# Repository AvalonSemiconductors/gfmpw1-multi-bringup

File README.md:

# GFMPW-1 Multi-project die bring-up

Contains all the files and tools used by me to bring up my [multi-project submission](https://github.com/AvalonSemiconductors/gfmpw1-multi) to GFMPW-1.

[Docs can be found here](https://avalonsemiconductors.github.io/GFMPW-1-MULTI/index.html)

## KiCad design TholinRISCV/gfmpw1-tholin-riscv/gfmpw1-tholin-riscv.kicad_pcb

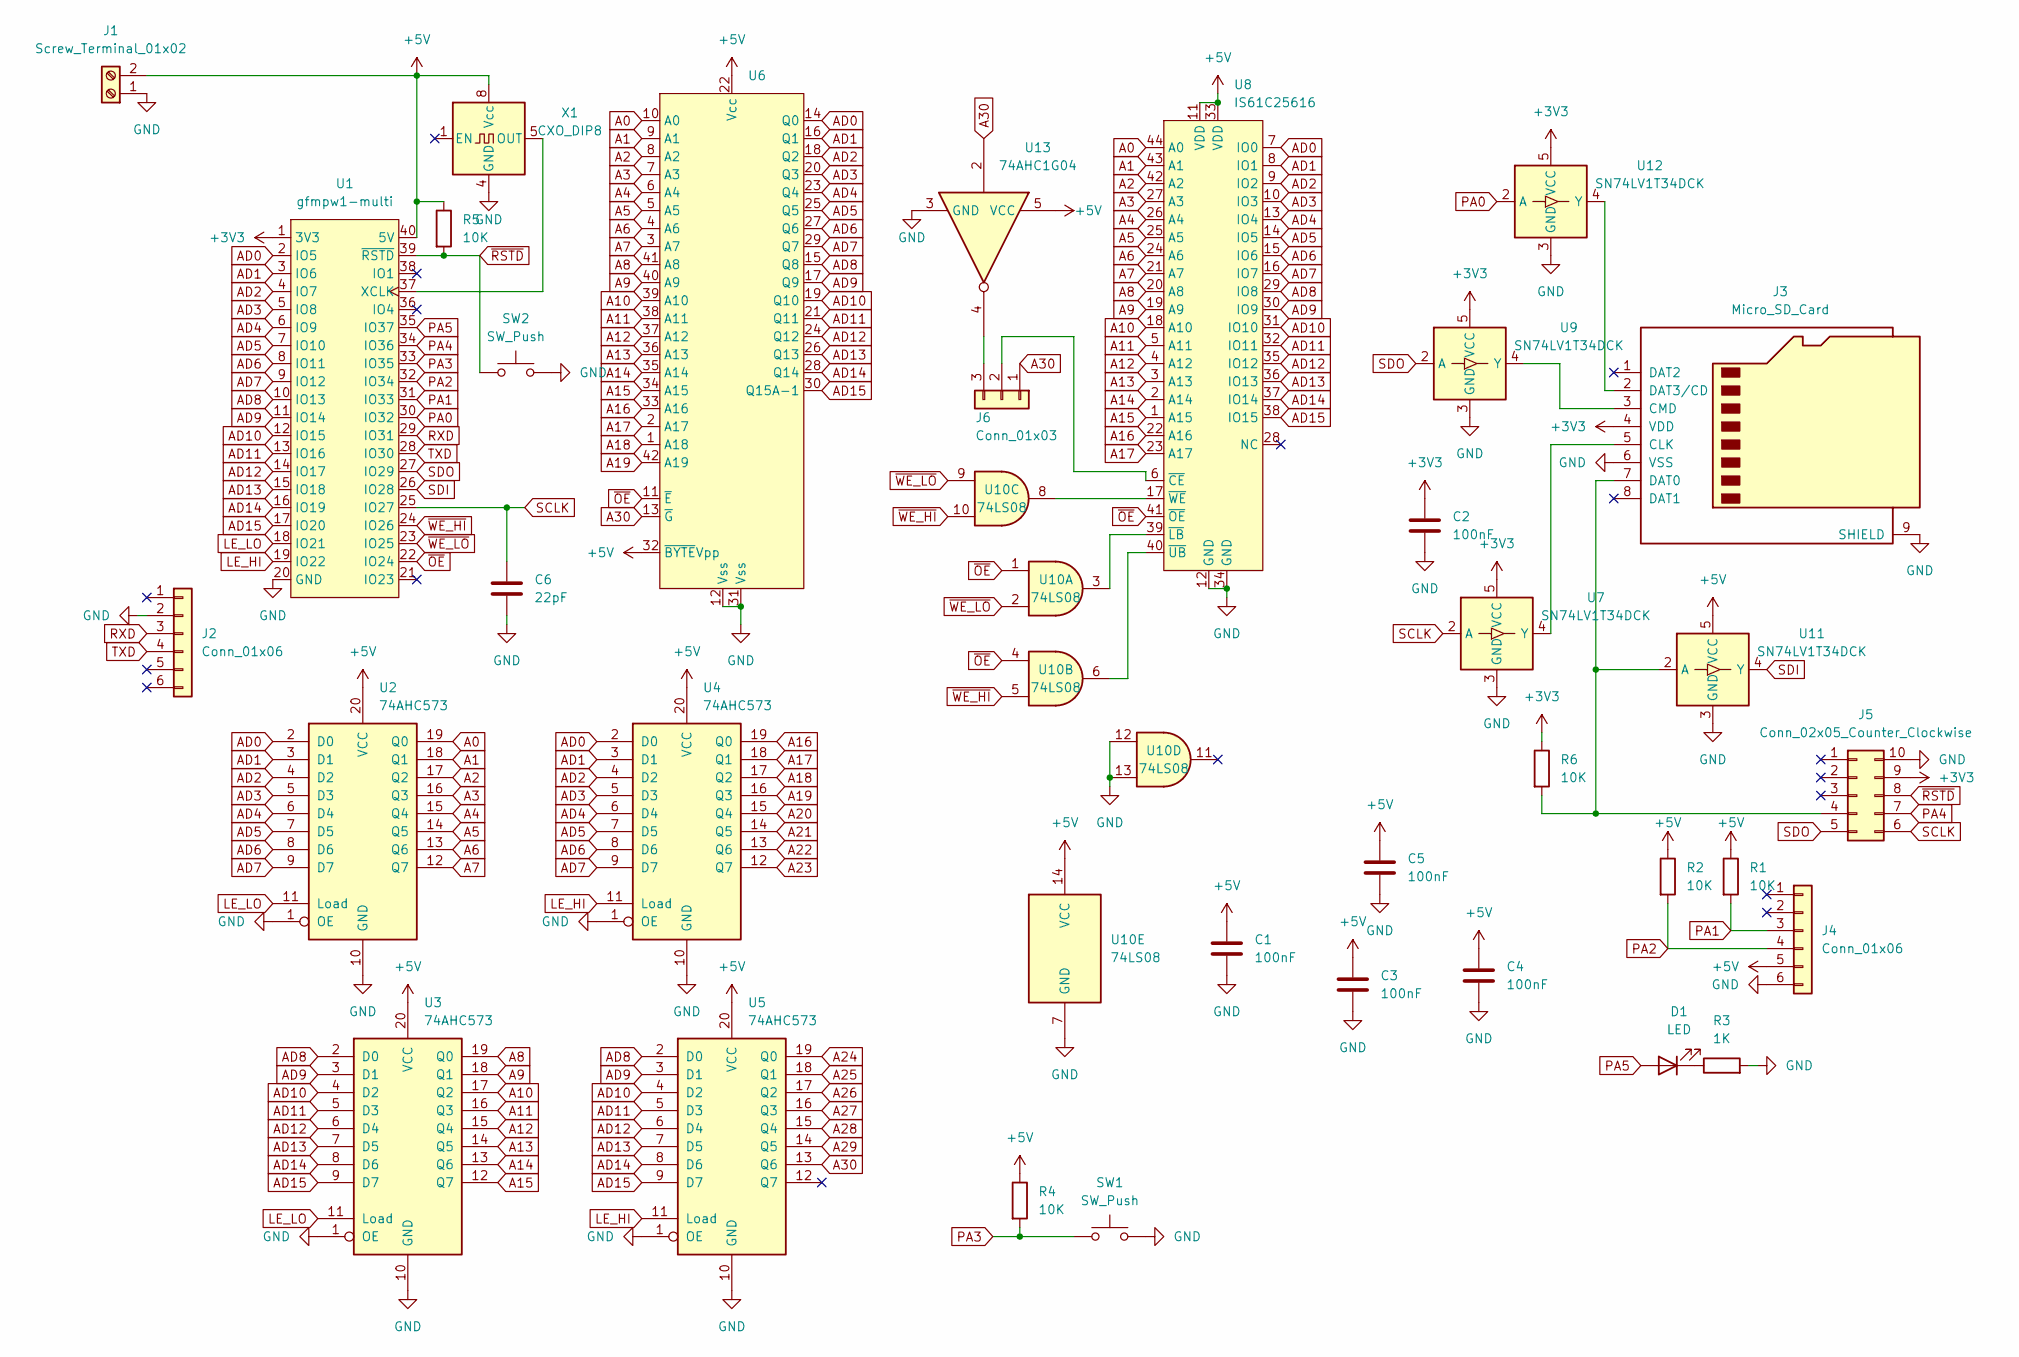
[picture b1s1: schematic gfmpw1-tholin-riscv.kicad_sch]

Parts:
C1, C2, C3, C4, C5: 100nF; C_Disc_D3.8mm_W2.6mm_P2.50mm
C6: 22pF; C_Disc_D3.8mm_W2.6mm_P2.50mm
D1: LED; LED_D5.0mm
J1: Screw_Terminal_01x02; TerminalBlock_bornier-2_P5.08mm
J2: Conn_01x06; PinSocket_1x06_P2.54mm_Vertical
J3: Micro_SD_Card; microSD_HC_Hirose_DM3AT-SF-PEJM5
J4: Conn_01x06; PinHeader_1x06_P2.54mm_Vertical
J5: Conn_02x05_Counter_Clockwise; PinHeader_2x05_P2.54mm_Vertical
J6: Conn_01x03; PinHeader_1x03_P2.54mm_Vertical
R1, R2, R4, R5, R6: 10K; R_Axial_DIN0204_L3.6mm_D1.6mm_P7.62mm_Horizontal
R3: 1K; R_Axial_DIN0204_L3.6mm_D1.6mm_P7.62mm_Horizontal
SW1, SW2: SW_Push; SW_PUSH_6mm
U1: gfmpw1-multi; DIP-40_W15.24mm_Socket
U2, U3, U4, U5: 74AHC573; TSSOP-20_4.4x6.5mm_P0.65mm
U6: DIP-42_W15.24mm
U7, U9, U11, U12: SN74LV1T34DCK; SOT-23-5
U8: IS61C25616; TSOP-II-44_10.16x18.41mm_P0.8mm
U10: 74LS08; SO-14_3.9x8.65mm_P1.27mm
U13: 74AHC1G04; SOIC-6
X1: CXO_DIP8; Oscillator_DIP-8

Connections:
+3V3: C2.1, J3.4 (VDD), J5.9, R6.1, U1.1 (3V3), U7.5 (VCC), U9.5 (VCC), U12.5 (VCC)
+5V: C1.1, C3.1, C4.1, C5.1, J1.2, J4.5, R1.1, R2.1, R4.1, R5.1, U1.40 (5V), U2.20 (VCC), U3.20 (VCC), U4.20 (VCC), U5.20 (VCC), U6.22 (Vcc), U6.32 (~BYTEVpp), U8.11 (VDD), U8.33 (VDD), U10.14 (VCC), U11.5 (VCC), U13.5 (VCC), X1.8 (Vcc)
A0: U2.19 (Q0), U6.10 (A0), U8.44 (A0)
A1: U2.18 (Q1), U6.9 (A1), U8.43 (A1)
A2: U2.17 (Q2), U6.8 (A2), U8.42 (A2)
A3: U2.16 (Q3), U6.7 (A3), U8.27 (A3)
A4: U2.15 (Q4), U6.6 (A4), U8.26 (A4)
A5: U2.14 (Q5), U6.5 (A5), U8.25 (A5)
A6: U2.13 (Q6), U6.4 (A6), U8.24 (A6)
A7: U2.12 (Q7), U6.3 (A7), U8.21 (A7)
A8: U3.19 (Q0), U6.41 (A8), U8.20 (A8)
A9: U3.18 (Q1), U6.40 (A9), U8.19 (A9)
A10: U3.17 (Q2), U6.39 (A10), U8.18 (A10)
A11: U3.16 (Q3), U6.38 (A11), U8.5 (A11)
A12: U3.15 (Q4), U6.37 (A12), U8.4 (A12)
A13: U3.14 (Q5), U6.36 (A13), U8.3 (A13)
A14: U3.13 (Q6), U6.35 (A14), U8.2 (A14)
A15: U3.12 (Q7), U6.34 (A15), U8.1 (A15)
A16: U4.19 (Q0), U6.33 (A16), U8.22 (A16)
A17: U4.18 (Q1), U6.2 (A17), U8.23 (A17)
A18: U4.17 (Q2), U6.1 (A18)
A19: U4.16 (Q3), U6.42 (A19)
A20: U4.15 (Q4)
A21: U4.14 (Q5)
A22: U4.13 (Q6)
A23: U4.12 (Q7)
A24: U5.19 (Q0)
A25: U5.18 (Q1)
A26: U5.17 (Q2)
A27: U5.16 (Q3)
A28: U5.15 (Q4)
A29: U5.14 (Q5)
A30: J6.1, U5.13 (Q6), U6.13 (~G), U13.2
AD0: U1.2 (IO5), U2.2 (D0), U4.2 (D0), U6.14 (Q0), U8.7 (IO0)
AD1: U1.3 (IO6), U2.3 (D1), U4.3 (D1), U6.16 (Q1), U8.8 (IO1)
AD2: U1.4 (IO7), U2.4 (D2), U4.4 (D2), U6.18 (Q2), U8.9 (IO2)
AD3: U1.5 (IO8), U2.5 (D3), U4.5 (D3), U6.20 (Q3), U8.10 (IO3)
AD4: U1.6 (IO9), U2.6 (D4), U4.6 (D4), U6.23 (Q4), U8.13 (IO4)
AD5: U1.7 (IO10), U2.7 (D5), U4.7 (D5), U6.25 (Q5), U8.14 (IO5)
AD6: U1.8 (IO11), U2.8 (D6), U4.8 (D6), U6.27 (Q6), U8.15 (IO6)
AD7: U1.9 (IO12), U2.9 (D7), U4.9 (D7), U6.29 (Q7), U8.16 (IO7)
AD8: U1.10 (IO13), U3.2 (D0), U5.2 (D0), U6.15 (Q8), U8.29 (IO8)
AD9: U1.11 (IO14), U3.3 (D1), U5.3 (D1), U6.17 (Q9), U8.30 (IO9)
AD10: U1.12 (IO15), U3.4 (D2), U5.4 (D2), U6.19 (Q10), U8.31 (IO10)
AD11: U1.13 (IO16), U3.5 (D3), U5.5 (D3), U6.21 (Q11), U8.32 (IO11)
AD12: U1.14 (IO17), U3.6 (D4), U5.6 (D4), U6.24 (Q12), U8.35 (IO12)
AD13: U1.15 (IO18), U3.7 (D5), U5.7 (D5), U6.26 (Q13), U8.36 (IO13)
AD14: U1.16 (IO19), U3.8 (D6), U5.8 (D6), U6.28 (Q14), U8.37 (IO14)
AD15: U1.17 (IO20), U3.9 (D7), U5.9 (D7), U6.30 (Q15A-1), U8.38 (IO15)
GND: C1.2, C2.2, C3.2, C4.2, C5.2, C6.2, J1.1, J2.2, J3.6 (VSS), J3.9 (SHIELD), J4.6, J5.10, R3.2, SW1.2, SW2.2, U1.20 (GND), U2.1 (OE), U2.10 (GND), U3.1 (OE), U3.10 (GND), U4.1 (OE), U4.10 (GND), U5.1 (OE), U5.10 (GND), U6.12 (Vss), U6.31 (Vss), U7.3 (GND), U8.12 (GND), U8.34 (GND), U9.3 (GND), U10.7 (GND), U10.12, U10.13, U11.3 (GND), U12.3 (GND), U13.3 (GND), X1.4 (GND)
LE_HI: U1.19 (IO22), U4.11 (Load), U5.11 (Load)
LE_LO: U1.18 (IO21), U2.11 (Load), U3.11 (Load)
unnamed: D1.1 (K), R3.1
unnamed: J3.5 (CLK), U7.4 (Y)
unnamed: J3.3 (CMD), U9.4 (Y)
unnamed: J3.7 (DAT0), J5.4, R6.2, U11.2 (A)
unnamed: J3.2 (DAT3/CD), U12.4 (Y)
unnamed: J6.2, U8.6 (~CE)
unnamed: J6.3, U13.4
unnamed: U1.37 (XCLK), X1.5 (OUT)
unnamed: U8.39 (~LB), U10.3
unnamed: U8.40 (~UB), U10.6
unnamed: U8.17 (~WE), U10.8
PA0: U1.30 (IO32), U12.2 (A)
PA1: J4.3, R1.2, U1.31 (IO33)
PA2: J4.4, R2.2, U1.32 (IO34)
PA3: R4.2, SW1.1, U1.33 (IO35)
PA4: J5.7, U1.34 (IO36)
PA5: D1.2 (A), U1.35 (IO37)
RXD: J2.3, U1.29 (IO31)
SCLK: C6.1, J5.6, U1.25 (IO27), U7.2 (A)
SDI: U1.26 (IO28), U11.4 (Y)
SDO: J5.5, U1.27 (IO29), U9.2 (A)
TXD: J2.4, U1.28 (IO30)
~OE: U1.22 (IO24), U6.11 (~E), U8.41 (~OE), U10.1, U10.4
~RSTD: J5.8, R5.2, SW2.1, U1.39 (~RSTD)
~WE_HI: U1.24 (IO26), U10.5, U10.10
~WE_LO: U1.23 (IO25), U10.2, U10.9

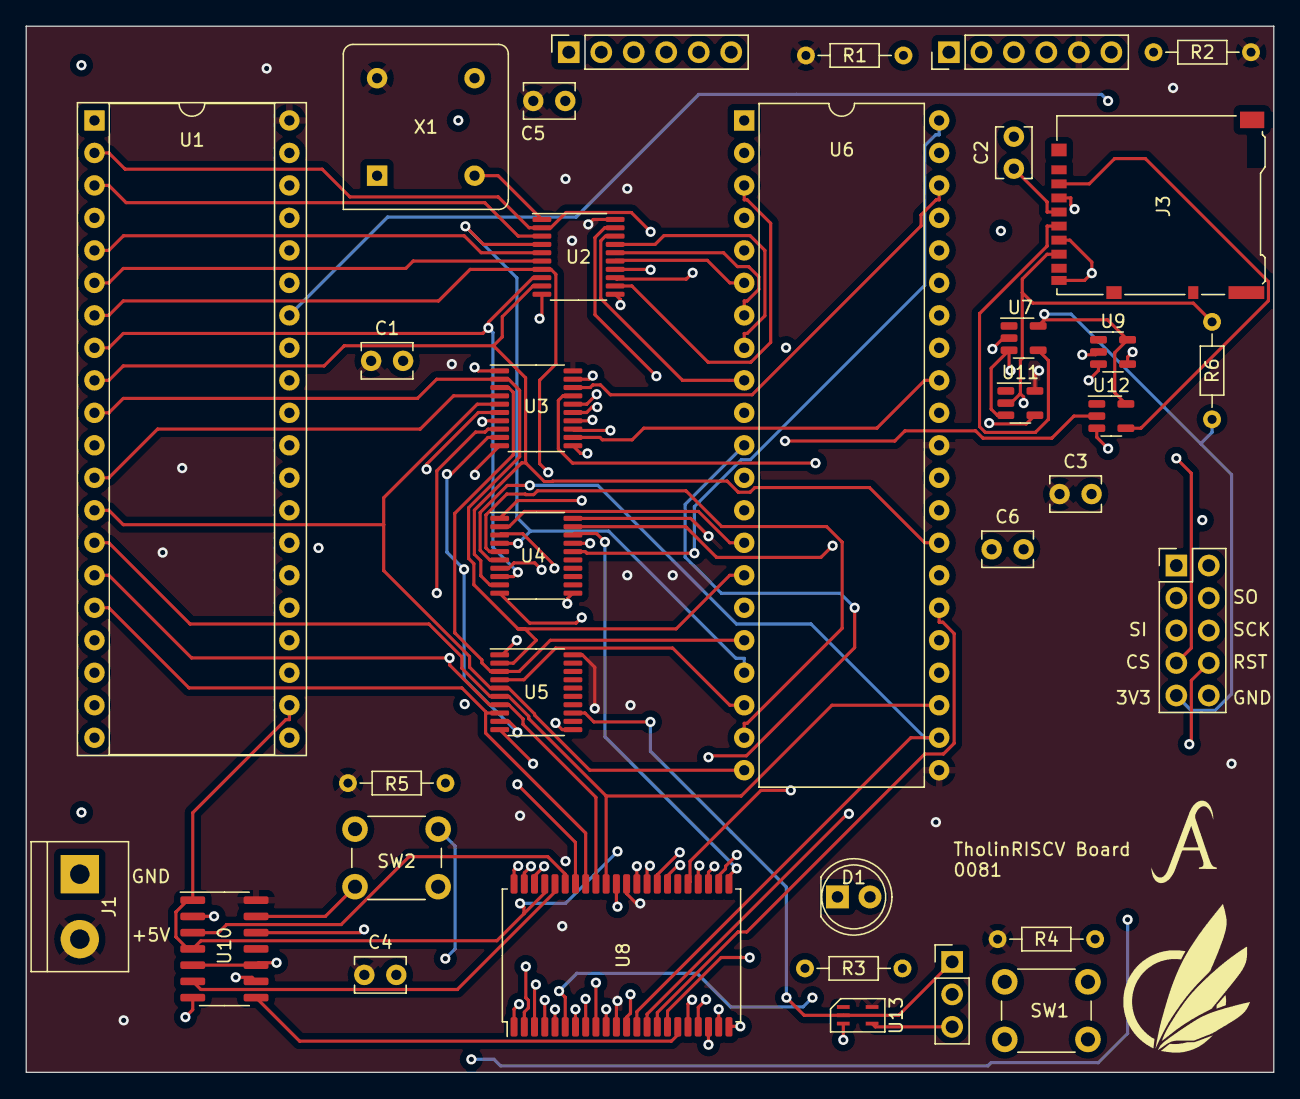
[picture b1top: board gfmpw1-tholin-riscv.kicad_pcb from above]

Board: 4 copper layers, 97.5 x 81.8 mm, 35 parts (0 on the bottom side), 68 nets.

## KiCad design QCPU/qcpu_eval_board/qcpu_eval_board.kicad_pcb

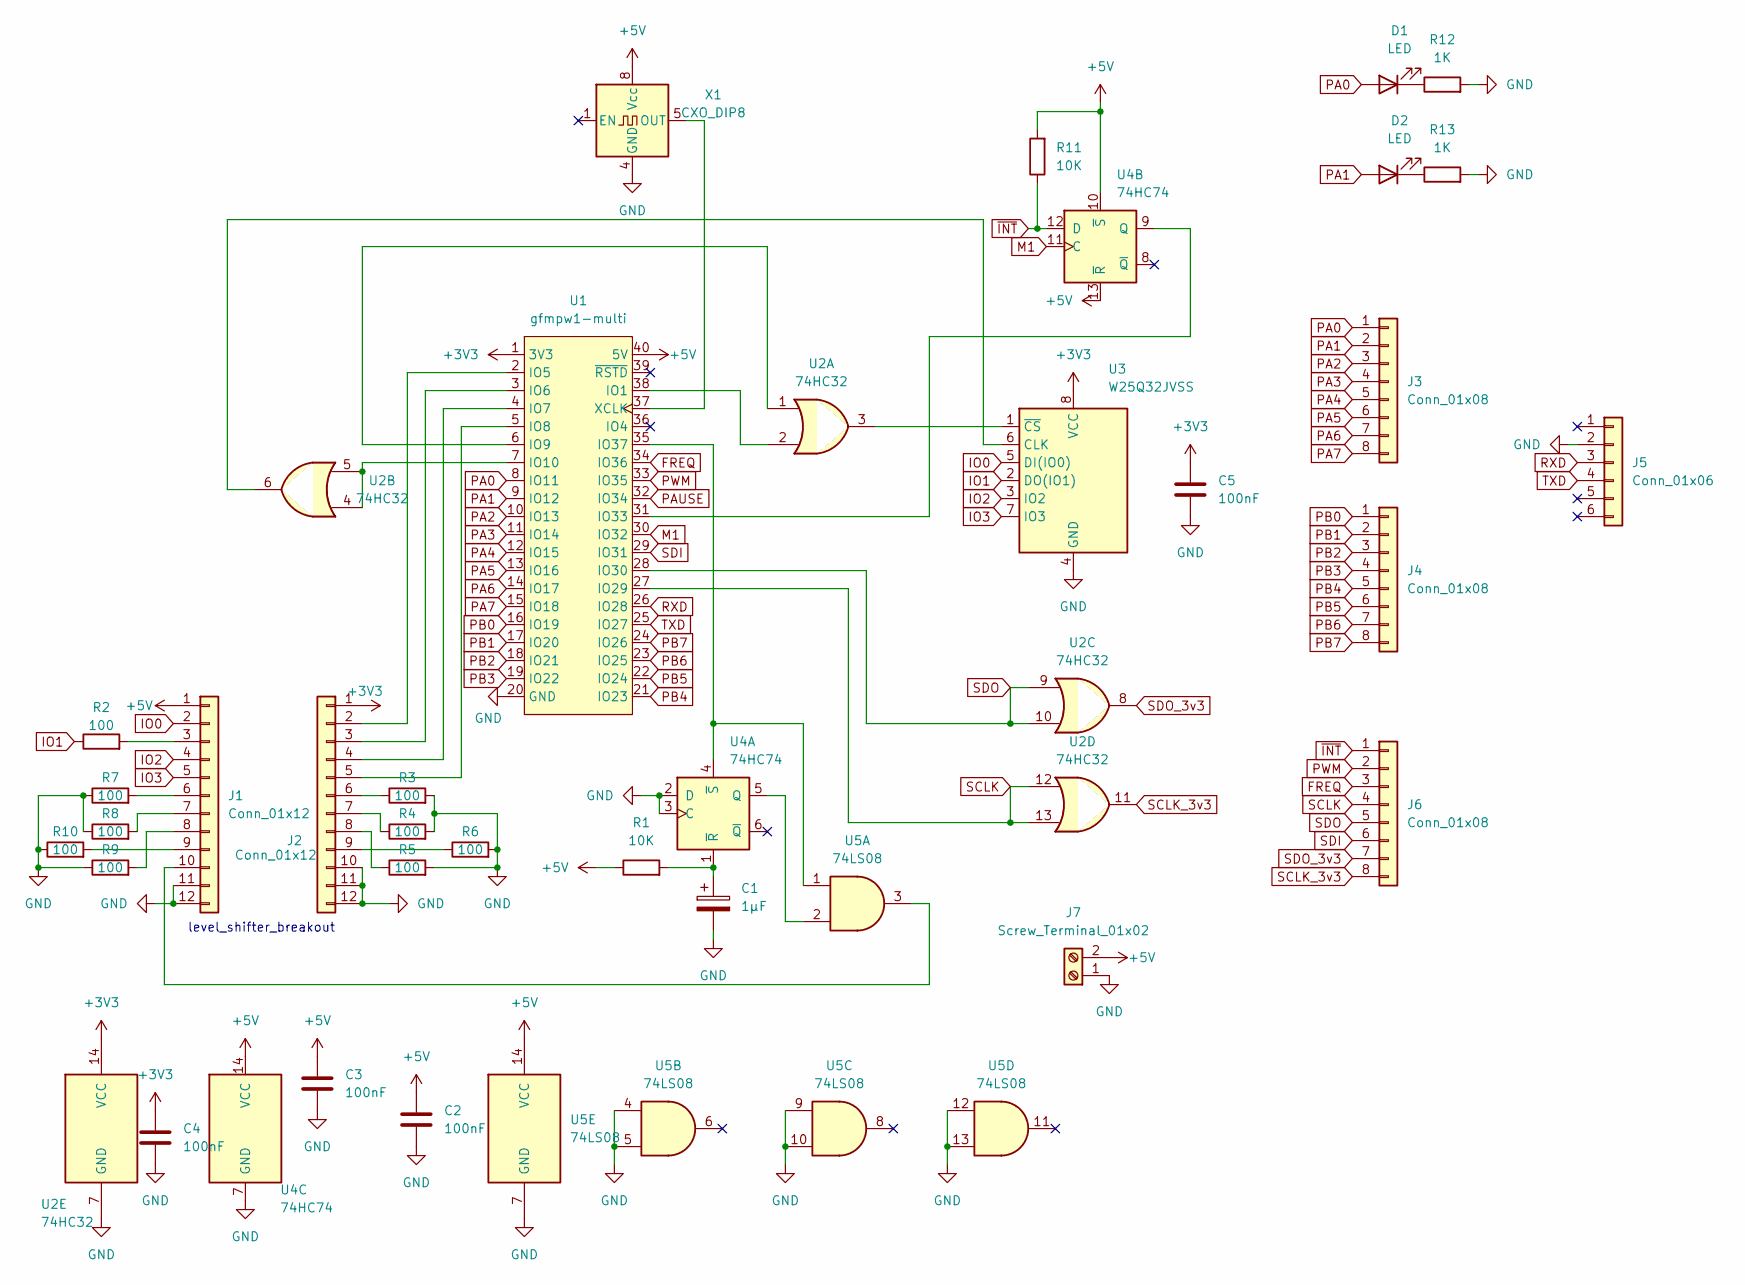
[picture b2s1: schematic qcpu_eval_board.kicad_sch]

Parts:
C1: 1µF; CP_Radial_D4.0mm_P2.00mm
C2, C3, C4, C5: 100nF; C_Disc_D3.8mm_W2.6mm_P2.50mm
D1, D2: LED; LED_D5.0mm
J1, J2: Conn_01x12; PinHeader_1x12_P2.54mm_Vertical
J3, J4, J6: Conn_01x08; PinHeader_1x08_P2.54mm_Vertical
J5: Conn_01x06; PinSocket_1x06_P2.54mm_Vertical
J7: Screw_Terminal_01x02; TerminalBlock_bornier-2_P5.08mm
R1, R11: 10K; R_Axial_DIN0204_L3.6mm_D1.6mm_P7.62mm_Horizontal
R2, R3, R4, R5, R6, R7, R8, R9, R10: 100; R_Axial_DIN0204_L3.6mm_D1.6mm_P7.62mm_Horizontal
R12, R13: 1K; R_Axial_DIN0204_L3.6mm_D1.6mm_P7.62mm_Horizontal
U1: gfmpw1-multi; DIP-40_W15.24mm_Socket
U2: 74HC32; DIP-14_W7.62mm
U3: W25Q32JVSS; DIP-8_W7.62mm
U4: 74HC74; DIP-14_W7.62mm
U5: 74LS08; DIP-14_W7.62mm
X1: CXO_DIP8; Oscillator_DIP-8

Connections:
+3V3: C4.1, C5.1, J2.1, U1.1 (3V3), U2.14 (VCC), U3.8 (VCC)
+5V: C2.1, C3.1, J1.1, J7.2, R1.1, R11.2, U1.40 (5V), U4.10 (~S), U4.13 (~R), U4.14 (VCC), U5.14 (VCC), X1.8 (Vcc)
FREQ: J6.3, U1.34 (IO36)
GND: C1.2, C2.2, C3.2, C4.2, C5.2, J1.11, J1.12, J2.10, J2.11, J2.12, J5.2, J7.1, R3.2, R4.2, R5.2, R6.2, R7.1, R8.1, R9.1, R10.1, R12.2, R13.2, U1.20 (GND), U2.7 (GND), U3.4 (GND), U4.2 (D), U4.3 (C), U4.7 (GND), U5.4, U5.5, U5.7 (GND), U5.9, U5.10, U5.12, U5.13, X1.4 (GND)
IO0: J1.2, U3.5 (DI(IO0))
IO1: R2.1, U3.2 (DO(IO1))
IO2: J1.4, U3.3 (IO2)
IO3: J1.5, U3.7 (IO3)
M1: U1.30 (IO32), U4.11 (C)
unnamed: D1.1 (K), R12.1
unnamed: D2.1 (K), R13.1
unnamed: J1.3, R2.2
unnamed: J1.6, R7.2
unnamed: J1.7, R8.2
unnamed: J1.8, R9.2
unnamed: J1.9, R10.2
unnamed: J1.10, U5.3
unnamed: J2.2, U1.2 (IO5)
unnamed: J2.3, U1.3 (IO6)
unnamed: J2.4, U1.4 (IO7)
unnamed: J2.5, U1.5 (IO8)
unnamed: J2.6, R3.1
unnamed: J2.7, R4.1
unnamed: J2.8, R5.1
unnamed: J2.9, R6.1
unnamed: U1.38 (IO1), U2.2
unnamed: U1.6 (IO9), U2.1
unnamed: U1.7 (IO10), U2.4, U2.5
unnamed: U1.31 (IO33), U4.9 (Q)
unnamed: U1.35 (IO37), U4.4 (~S), U5.1
unnamed: U1.37 (XCLK), X1.5 (OUT)
unnamed: U2.6, U3.6 (CLK)
unnamed: U2.3, U3.1 (~CS)
unnamed: U4.5 (Q), U5.2
unnamed: C1.1, R1.2, U4.1 (~R)
PA0: D1.2 (A), J3.1, U1.8 (IO11)
PA1: D2.2 (A), J3.2, U1.9 (IO12)
PA2: J3.3, U1.10 (IO13)
PA3: J3.4, U1.11 (IO14)
PA4: J3.5, U1.12 (IO15)
PA5: J3.6, U1.13 (IO16)
PA6: J3.7, U1.14 (IO17)
PA7: J3.8, U1.15 (IO18)
PAUSE: U1.32 (IO34)
PB0: J4.1, U1.16 (IO19)
PB1: J4.2, U1.17 (IO20)
PB2: J4.3, U1.18 (IO21)
PB3: J4.4, U1.19 (IO22)
PB4: J4.5, U1.21 (IO23)
PB5: J4.6, U1.22 (IO24)
PB6: J4.7, U1.23 (IO25)
PB7: J4.8, U1.24 (IO26)
PWM: J6.2, U1.33 (IO35)
RXD: J5.3, U1.26 (IO28)
SCLK: J6.4, U1.27 (IO29), U2.12, U2.13
SCLK_3v3: J6.8, U2.11
SDI: J6.6, U1.29 (IO31)
SDO: J6.5, U1.28 (IO30), U2.9, U2.10
SDO_3v3: J6.7, U2.8
TXD: J5.4, U1.25 (IO27)
~INT: J6.1, R11.1, U4.12 (D)

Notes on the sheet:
level_shifter_breakout

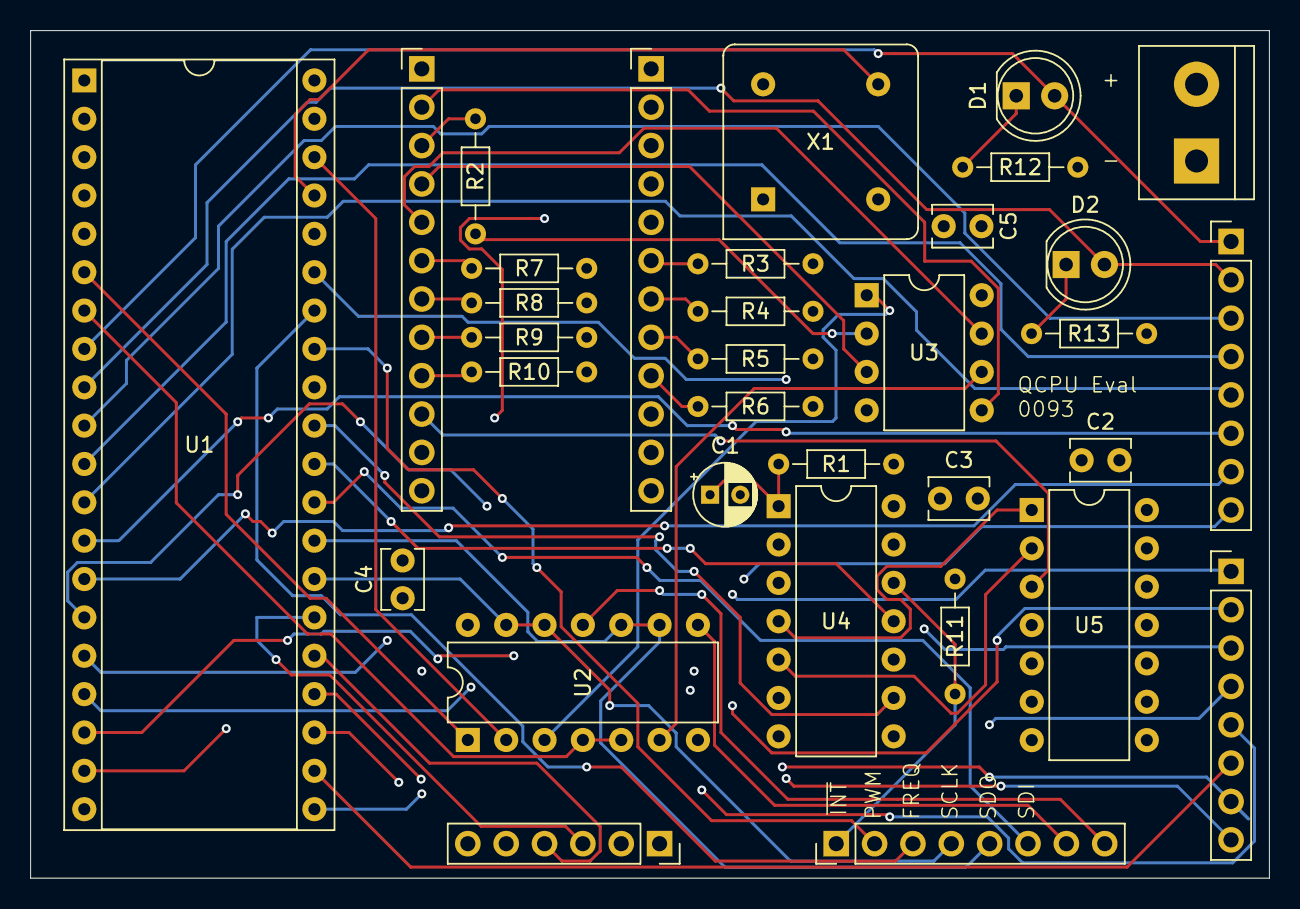
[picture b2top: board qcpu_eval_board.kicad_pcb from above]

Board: 4 copper layers, 82.0 x 56.1 mm, 33 parts (0 on the bottom side), 60 nets.

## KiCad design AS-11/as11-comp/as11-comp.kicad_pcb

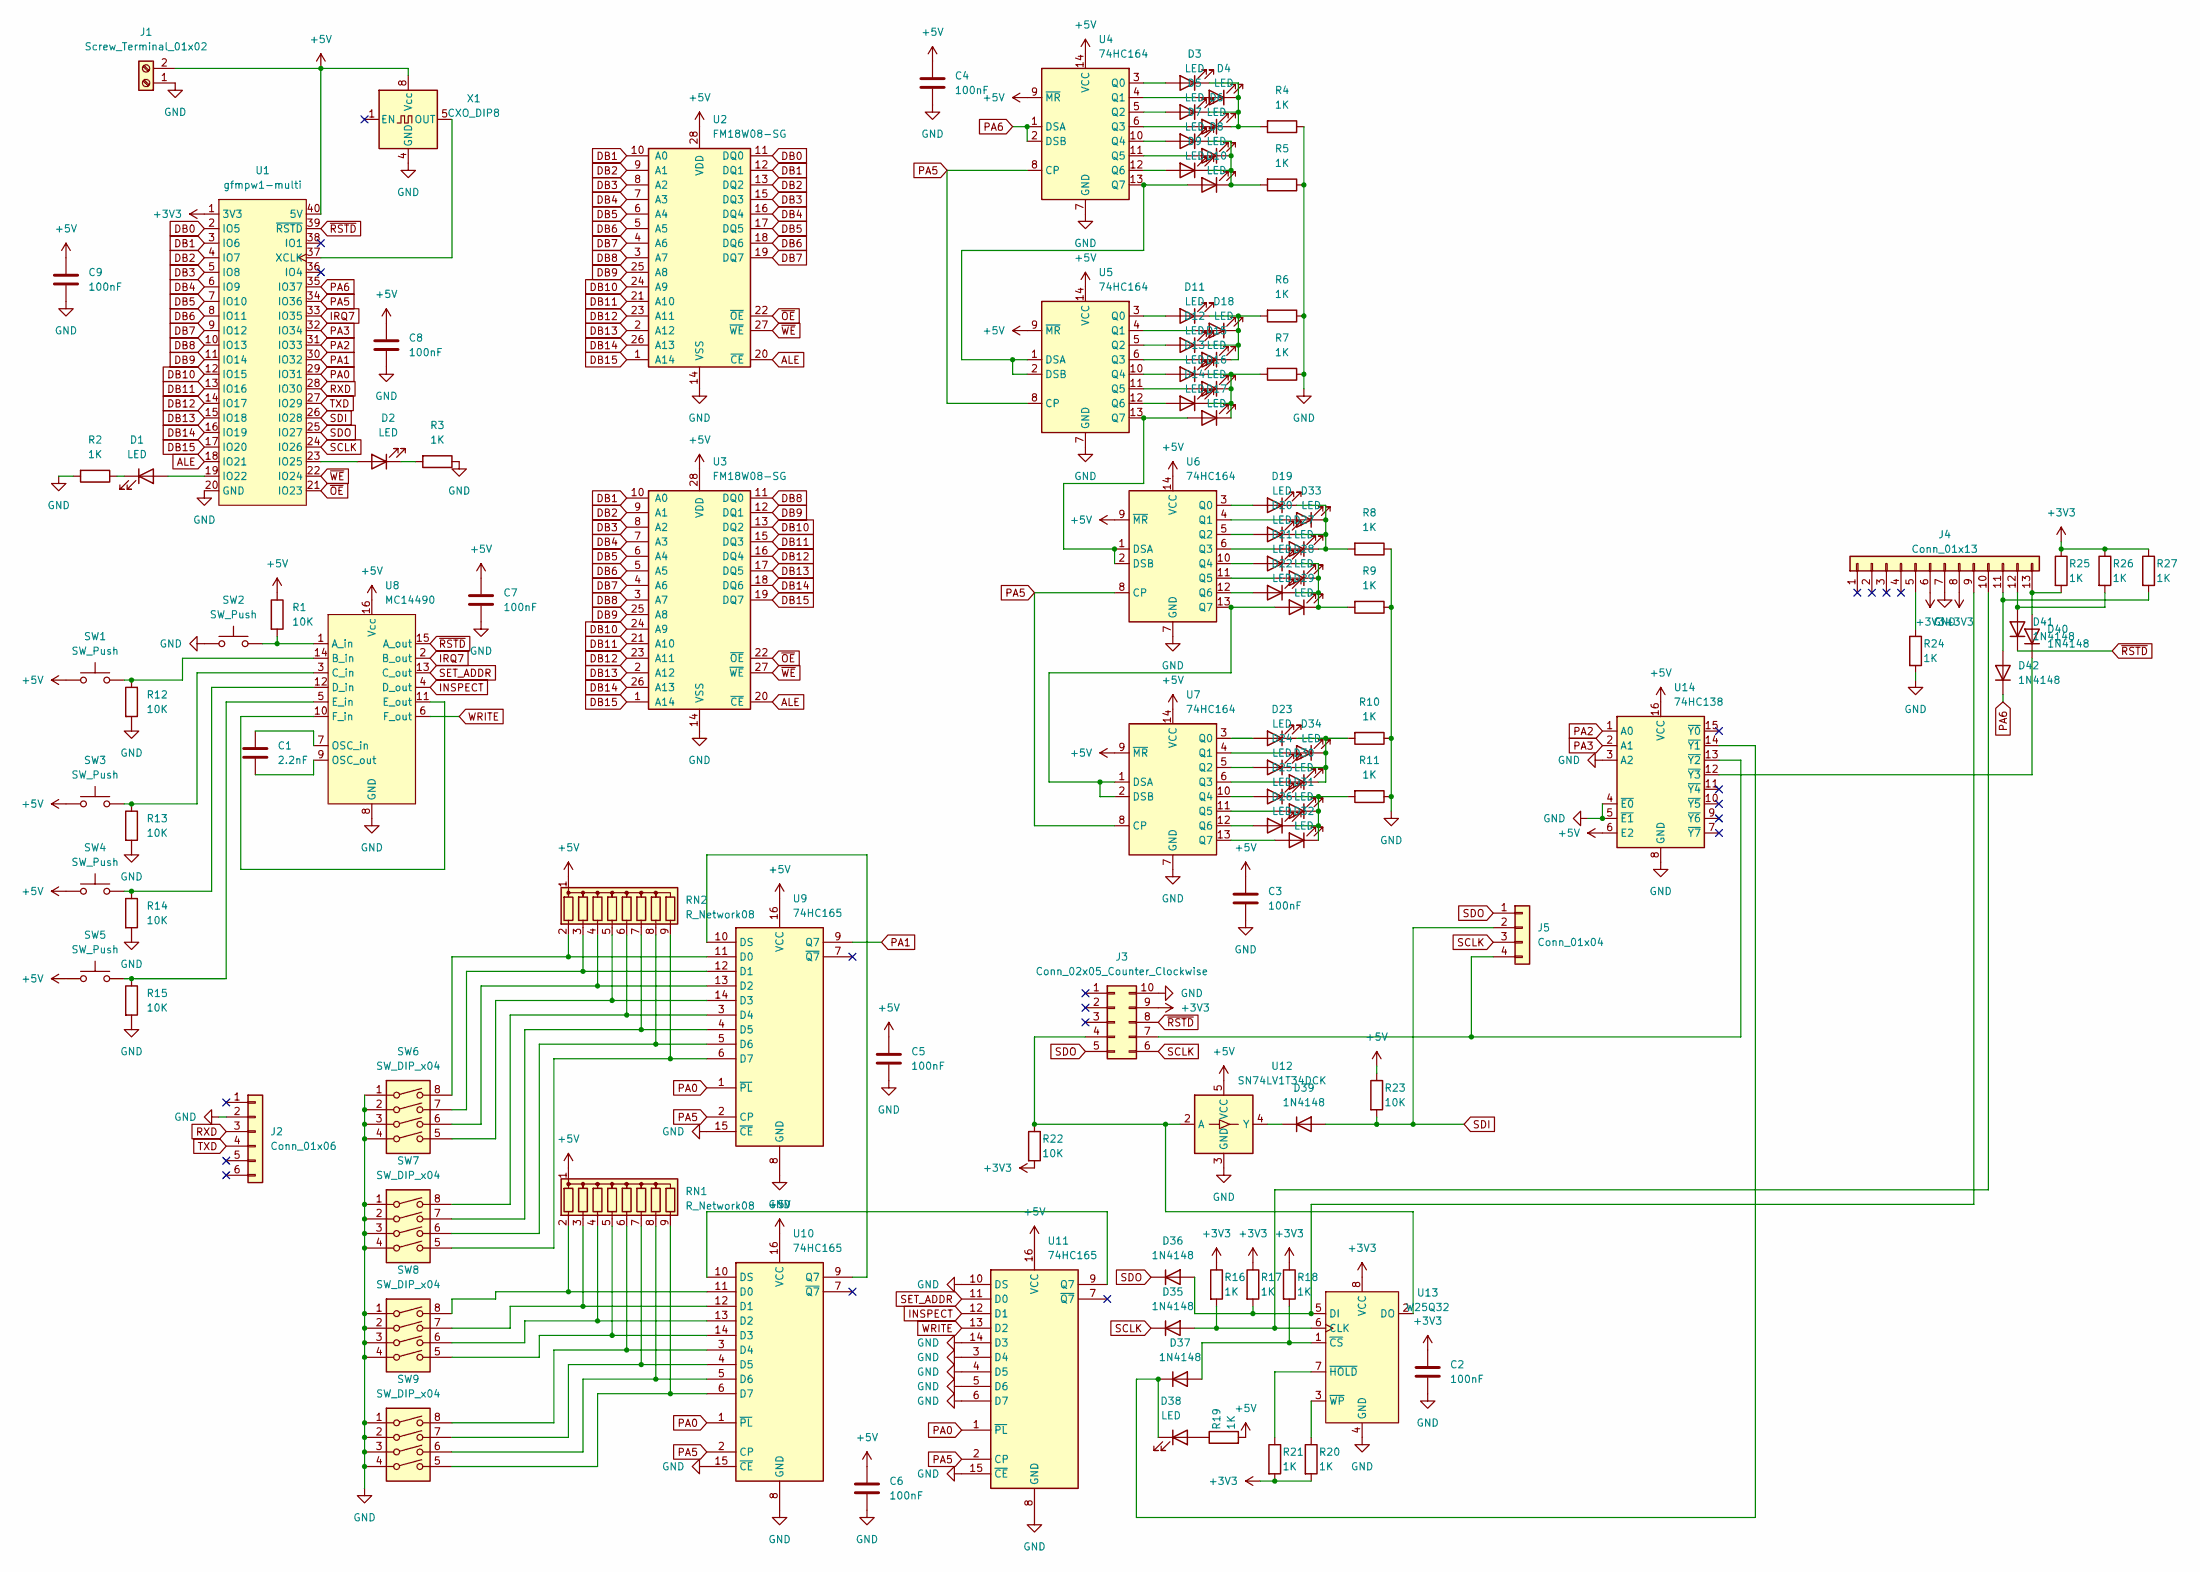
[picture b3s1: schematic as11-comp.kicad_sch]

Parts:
C1: 2.2nF; C_Disc_D3.8mm_W2.6mm_P2.50mm
C2, C3, C4, C5, C6, C7, C8, C9: 100nF; C_Disc_D3.4mm_W2.1mm_P2.50mm
D1, D2, D3, D4, D5, D6, D7, D8, D9, D10, D11, D12, D13, D14, D15, D16, D17, D18, D19, D20, D21, D22, D23, D24, D25, D26, D27, D28, D29, D30, D31, D32, D33, D34, D38: LED; LED_1206_3216Metric_Pad1.42x1.75mm_HandSolder
D35, D36, D37, D39, D40, D41, D42: 1N4148; D_DO-34_SOD68_P7.62mm_Horizontal
J1: Screw_Terminal_01x02; TerminalBlock_bornier-2_P5.08mm
J2: Conn_01x06; PinSocket_1x06_P2.54mm_Vertical
J3: Conn_02x05_Counter_Clockwise; PinHeader_2x05_P2.54mm_Vertical
J4: Conn_01x13; PinHeader_1x13_P2.54mm_Vertical
J5: Conn_01x04; PinHeader_1x04_P2.54mm_Vertical
R1, R12, R13, R14, R15: 10K; R_Axial_DIN0204_L3.6mm_D1.6mm_P7.62mm_Horizontal
R2, R3, R4, R5, R6, R7, R8, R9, R10, R11, R16, R17, R18, R19, R20, R21, R24, R25, R26, R27: 1K; R_1206_3216Metric_Pad1.30x1.75mm_HandSolder
R22, R23: 10K; R_1206_3216Metric_Pad1.30x1.75mm_HandSolder
RN1, RN2: R_Network08; R_Array_SIP9
SW1, SW2, SW3, SW4, SW5: SW_Push; SW_PUSH_6mm
SW6, SW7, SW8, SW9: SW_DIP_x04; SW_DIP_SPSTx04_Slide_6.7x11.72mm_W8.61mm_P2.54mm_LowProfile
U1: gfmpw1-multi; DIP-40_W15.24mm_Socket
U2, U3: FM18W08-SG; DIP-28_W15.24mm
U4, U5, U6, U7: 74HC164; SO-14_3.9x8.65mm_P1.27mm
U8: MC14490; DIP-16_W7.62mm
U9, U10, U11: 74HC165; SO-16_3.9x9.9mm_P1.27mm
U12: SN74LV1T34DCK; SOT-23-5
U13: W25Q32; DIP-8_W7.62mm
U14: 74HC138; SO-16_3.9x9.9mm_P1.27mm
X1: CXO_DIP8; Oscillator_DIP-8

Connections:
+3V3: C2.1, J3.9, J4.6, J4.8, R16.1, R17.1, R18.1, R20.2, R21.2, R22.2, R25.1, R26.1, R27.1, U1.1 (3V3), U13.8 (VCC)
+5V: C3.1, C4.1, C5.1, C6.1, C7.1, C8.1, C9.1, J1.2, R1.1, R19.2, R23.1, RN1.1 (common), RN2.1 (common), SW1.1, SW3.1, SW4.1, SW5.1, U1.40 (5V), U2.28 (VDD), U3.28 (VDD), U4.9 (~MR), U4.14 (VCC), U5.9 (~MR), U5.14 (VCC), U6.9 (~MR), U6.14 (VCC), U7.9 (~MR), U7.14 (VCC), U8.16 (Vcc), U9.16 (VCC), U10.16 (VCC), U11.16 (VCC), U12.5 (VCC), U14.6 (E2), U14.16 (VCC), X1.8 (Vcc)
ALE: U1.18 (IO21), U2.20 (~CE), U3.20 (~CE)
DB0: U1.2 (IO5), U2.11 (DQ0)
DB1: U1.3 (IO6), U2.10 (A0), U2.12 (DQ1), U3.10 (A0)
DB2: U1.4 (IO7), U2.9 (A1), U2.13 (DQ2), U3.9 (A1)
DB3: U1.5 (IO8), U2.8 (A2), U2.15 (DQ3), U3.8 (A2)
DB4: U1.6 (IO9), U2.7 (A3), U2.16 (DQ4), U3.7 (A3)
DB5: U1.7 (IO10), U2.6 (A4), U2.17 (DQ5), U3.6 (A4)
DB6: U1.8 (IO11), U2.5 (A5), U2.18 (DQ6), U3.5 (A5)
DB7: U1.9 (IO12), U2.4 (A6), U2.19 (DQ7), U3.4 (A6)
DB8: U1.10 (IO13), U2.3 (A7), U3.3 (A7), U3.11 (DQ0)
DB9: U1.11 (IO14), U2.25 (A8), U3.12 (DQ1), U3.25 (A8)
DB10: U1.12 (IO15), U2.24 (A9), U3.13 (DQ2), U3.24 (A9)
DB11: U1.13 (IO16), U2.21 (A10), U3.15 (DQ3), U3.21 (A10)
DB12: U1.14 (IO17), U2.23 (A11), U3.16 (DQ4), U3.23 (A11)
DB13: U1.15 (IO18), U2.2 (A12), U3.2 (A12), U3.17 (DQ5)
DB14: U1.16 (IO19), U2.26 (A13), U3.18 (DQ6), U3.26 (A13)
DB15: U1.17 (IO20), U2.1 (A14), U3.1 (A14), U3.19 (DQ7)
GND: C2.2, C3.2, C4.2, C5.2, C6.2, C7.2, C8.2, C9.2, J1.1, J2.2, J3.10, J4.7, R2.2, R3.1, R4.1, R5.1, R6.1, R7.1, R8.1, R9.1, R10.1, R11.1, R12.2, R13.2, R14.2, R15.2, R24.2, SW2.1, SW6.1, SW6.2, SW6.3, SW6.4, SW7.1, SW7.2, SW7.3, SW7.4, SW8.1, SW8.2, SW8.3, SW8.4, SW9.1, SW9.2, SW9.3, SW9.4, U1.20 (GND), U2.14 (VSS), U3.14 (VSS), U4.7 (GND), U5.7 (GND), U6.7 (GND), U7.7 (GND), U8.8 (GND), U9.8 (GND), U9.15 (~CE), U10.8 (GND), U10.15 (~CE), U11.3 (D4), U11.4 (D5), U11.5 (D6), U11.6 (D7), U11.8 (GND), U11.10 (DS), U11.14 (D3), U11.15 (~CE), U12.3 (GND), U13.4 (GND), U14.3 (A2), U14.4 (~E0), U14.5 (~E1), U14.8 (GND), X1.4 (GND)
INSPECT: U8.4 (D_out), U11.12 (D1)
IRQ7: U1.33 (IO35), U8.2 (B_out)
unnamed: D1.2 (A), U1.19 (IO22)
unnamed: D1.1 (K), R2.1
unnamed: D2.2 (A), U1.23 (IO25)
unnamed: D2.1 (K), R3.2
unnamed: D3.2 (A), U4.3 (Q0)
unnamed: D3.1 (K), D4.1 (K), D5.1 (K), D6.1 (K), R4.2
unnamed: D4.2 (A), U4.4 (Q1)
unnamed: D5.2 (A), U4.5 (Q2)
unnamed: D6.2 (A), U4.6 (Q3)
unnamed: D7.2 (A), U4.10 (Q4)
unnamed: D8.2 (A), U4.11 (Q5)
unnamed: D9.2 (A), U4.12 (Q6)
unnamed: D10.2 (A), U4.13 (Q7), U5.1 (DSA), U5.2 (DSB)
unnamed: D7.1 (K), D8.1 (K), D9.1 (K), D10.1 (K), R5.2
unnamed: D11.2 (A), U5.3 (Q0)
unnamed: D11.1 (K), D12.1 (K), D15.1 (K), D18.1 (K), R6.2
unnamed: D12.2 (A), U5.5 (Q2)
unnamed: D13.2 (A), U5.10 (Q4)
unnamed: D13.1 (K), D14.1 (K), D16.1 (K), D17.1 (K), R7.2
unnamed: D14.2 (A), U5.12 (Q6)
unnamed: D15.2 (A), U5.6 (Q3)
unnamed: D16.2 (A), U5.11 (Q5)
unnamed: D17.2 (A), U5.13 (Q7), U6.1 (DSA), U6.2 (DSB)
unnamed: D18.2 (A), U5.4 (Q1)
unnamed: D19.2 (A), U6.3 (Q0)
unnamed: D19.1 (K), D20.1 (K), D27.1 (K), D33.1 (K), R8.2
unnamed: D20.2 (A), U6.5 (Q2)
unnamed: D21.2 (A), U6.10 (Q4)
unnamed: D21.1 (K), D22.1 (K), D28.1 (K), D29.1 (K), R9.2
unnamed: D22.2 (A), U6.12 (Q6)
unnamed: D23.2 (A), U7.3 (Q0)
unnamed: D23.1 (K), D24.1 (K), D30.1 (K), D34.1 (K), R10.2
unnamed: D24.2 (A), U7.5 (Q2)
unnamed: D25.2 (A), U7.10 (Q4)
unnamed: D25.1 (K), D26.1 (K), D31.1 (K), D32.1 (K), R11.2
unnamed: D26.2 (A), U7.12 (Q6)
unnamed: D27.2 (A), U6.6 (Q3)
unnamed: D28.2 (A), U6.11 (Q5)
unnamed: D29.2 (A), U6.13 (Q7), U7.1 (DSA), U7.2 (DSB)
unnamed: D30.2 (A), U7.6 (Q3)
unnamed: D31.2 (A), U7.11 (Q5)
unnamed: D32.2 (A), U7.13 (Q7)
unnamed: D33.2 (A), U6.4 (Q1)
unnamed: D34.2 (A), U7.4 (Q1)
unnamed: D35.2 (A), J4.10, R16.2, U13.6 (CLK)
unnamed: D36.2 (A), J4.9, R17.2, U13.5 (DI)
unnamed: D37.2 (A), R18.2, U13.1 (~CS)
unnamed: D37.1 (K), D38.1 (K), U14.14 (~Y1)
unnamed: D38.2 (A), R19.1
unnamed: D39.1 (K), U12.4 (Y)
unnamed: D40.2 (A), J4.13, R25.2
unnamed: D40.1 (K), U14.12 (~Y3)
unnamed: D41.2 (A), J4.12, R26.2
unnamed: D42.2 (A), J4.11, R27.2
unnamed: J3.4, R22.1, U12.2 (A), U13.2 (DO)
unnamed: J3.7, J5.4, U14.13 (~Y2)
unnamed: J4.5, R24.1
unnamed: RN1.2 (R1), SW8.8, U10.11 (D0)
unnamed: RN1.3 (R2), SW8.7, U10.12 (D1)
unnamed: RN1.4 (R3), SW8.6, U10.13 (D2)
unnamed: RN1.5 (R4), SW8.5, U10.14 (D3)
unnamed: RN1.6 (R5), SW9.8, U10.3 (D4)
unnamed: RN1.7 (R6), SW9.7, U10.4 (D5)
unnamed: RN1.8 (R7), SW9.6, U10.5 (D6)
unnamed: RN1.9 (R8), SW9.5, U10.6 (D7)
unnamed: RN2.2 (R1), SW6.8, U9.11 (D0)
unnamed: RN2.3 (R2), SW6.7, U9.12 (D1)
unnamed: RN2.4 (R3), SW6.6, U9.13 (D2)
unnamed: RN2.5 (R4), SW6.5, U9.14 (D3)
unnamed: RN2.6 (R5), SW7.8, U9.3 (D4)
unnamed: RN2.7 (R6), SW7.7, U9.4 (D5)
unnamed: RN2.8 (R7), SW7.6, U9.5 (D6)
unnamed: RN2.9 (R8), SW7.5, U9.6 (D7)
unnamed: U1.37 (XCLK), X1.5 (OUT)
unnamed: R1.2, SW2.2, U8.1 (A_in)
unnamed: R12.1, SW1.2, U8.14 (B_in)
unnamed: R13.1, SW3.2, U8.3 (C_in)
unnamed: R14.1, SW4.2, U8.12 (D_in)
unnamed: R15.1, SW5.2, U8.5 (E_in)
unnamed: U8.10 (F_in), U8.11 (E_out)
unnamed: C1.2, U8.7 (OSC_in)
unnamed: C1.1, U8.9 (OSC_out)
unnamed: U10.10 (DS), U11.9 (Q7)
unnamed: U9.10 (DS), U10.9 (Q7)
unnamed: R21.1, U13.7 (~HOLD)
unnamed: R20.1, U13.3 (~WP)
PA0: U1.29 (IO31), U9.1 (~PL), U10.1 (~PL), U11.1 (~PL)
PA1: U1.30 (IO32), U9.9 (Q7)
PA2: U1.31 (IO33), U14.1 (A0)
PA3: U1.32 (IO34), U14.2 (A1)
PA5: U1.34 (IO36), U4.8 (CP), U5.8 (CP), U6.8 (CP), U7.8 (CP), U9.2 (CP), U10.2 (CP), U11.2 (CP)
PA6: D42.1 (K), U1.35 (IO37), U4.1 (DSA), U4.2 (DSB)
RXD: J2.3, U1.28 (IO30)
SCLK: D35.1 (K), J3.6, J5.3, U1.24 (IO26)
SDI: D39.2 (A), J5.2, R23.2, U1.26 (IO28)
SDO: D36.1 (K), J3.5, J5.1, U1.25 (IO27)
SET_ADDR: U8.13 (C_out), U11.11 (D0)
TXD: J2.4, U1.27 (IO29)
WRITE: U8.6 (F_out), U11.13 (D2)
~OE: U1.21 (IO23), U2.22 (~OE), U3.22 (~OE)
~RSTD: D41.1 (K), J3.8, U1.39 (~RSTD), U8.15 (A_out)
~WE: U1.22 (IO24), U2.27 (~WE), U3.27 (~WE)

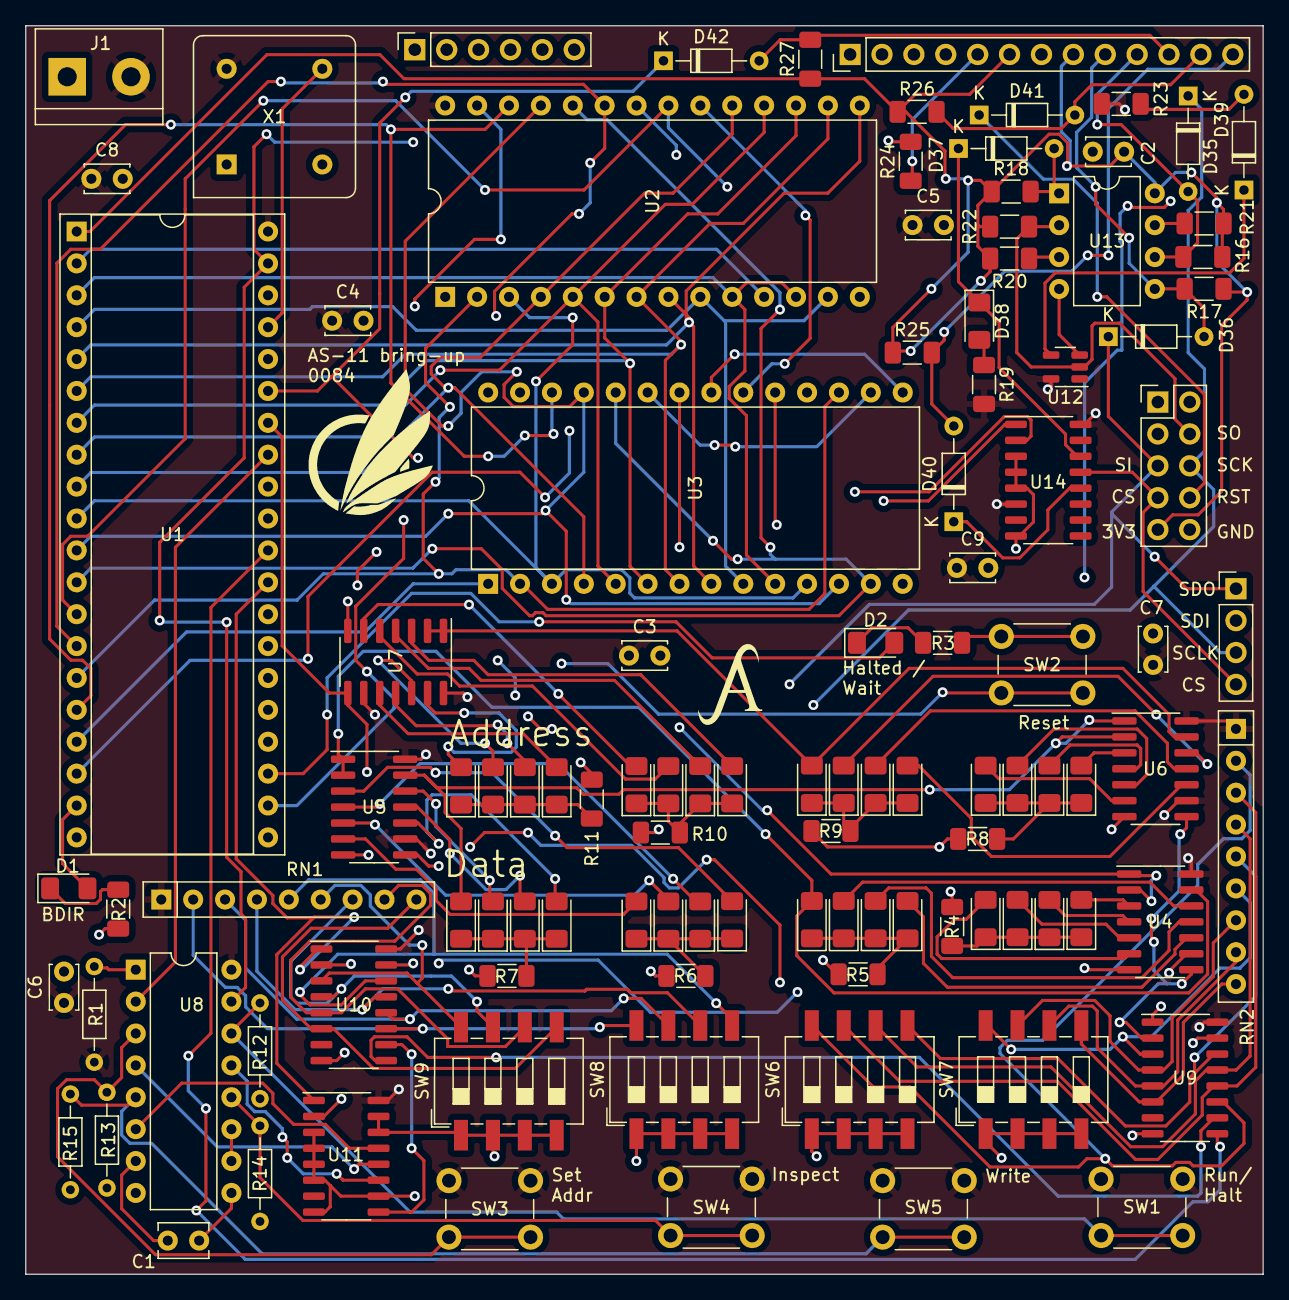
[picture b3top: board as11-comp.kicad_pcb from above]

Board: 4 copper layers, 98.6 x 99.4 mm, 109 parts (0 on the bottom side), 124 nets.
